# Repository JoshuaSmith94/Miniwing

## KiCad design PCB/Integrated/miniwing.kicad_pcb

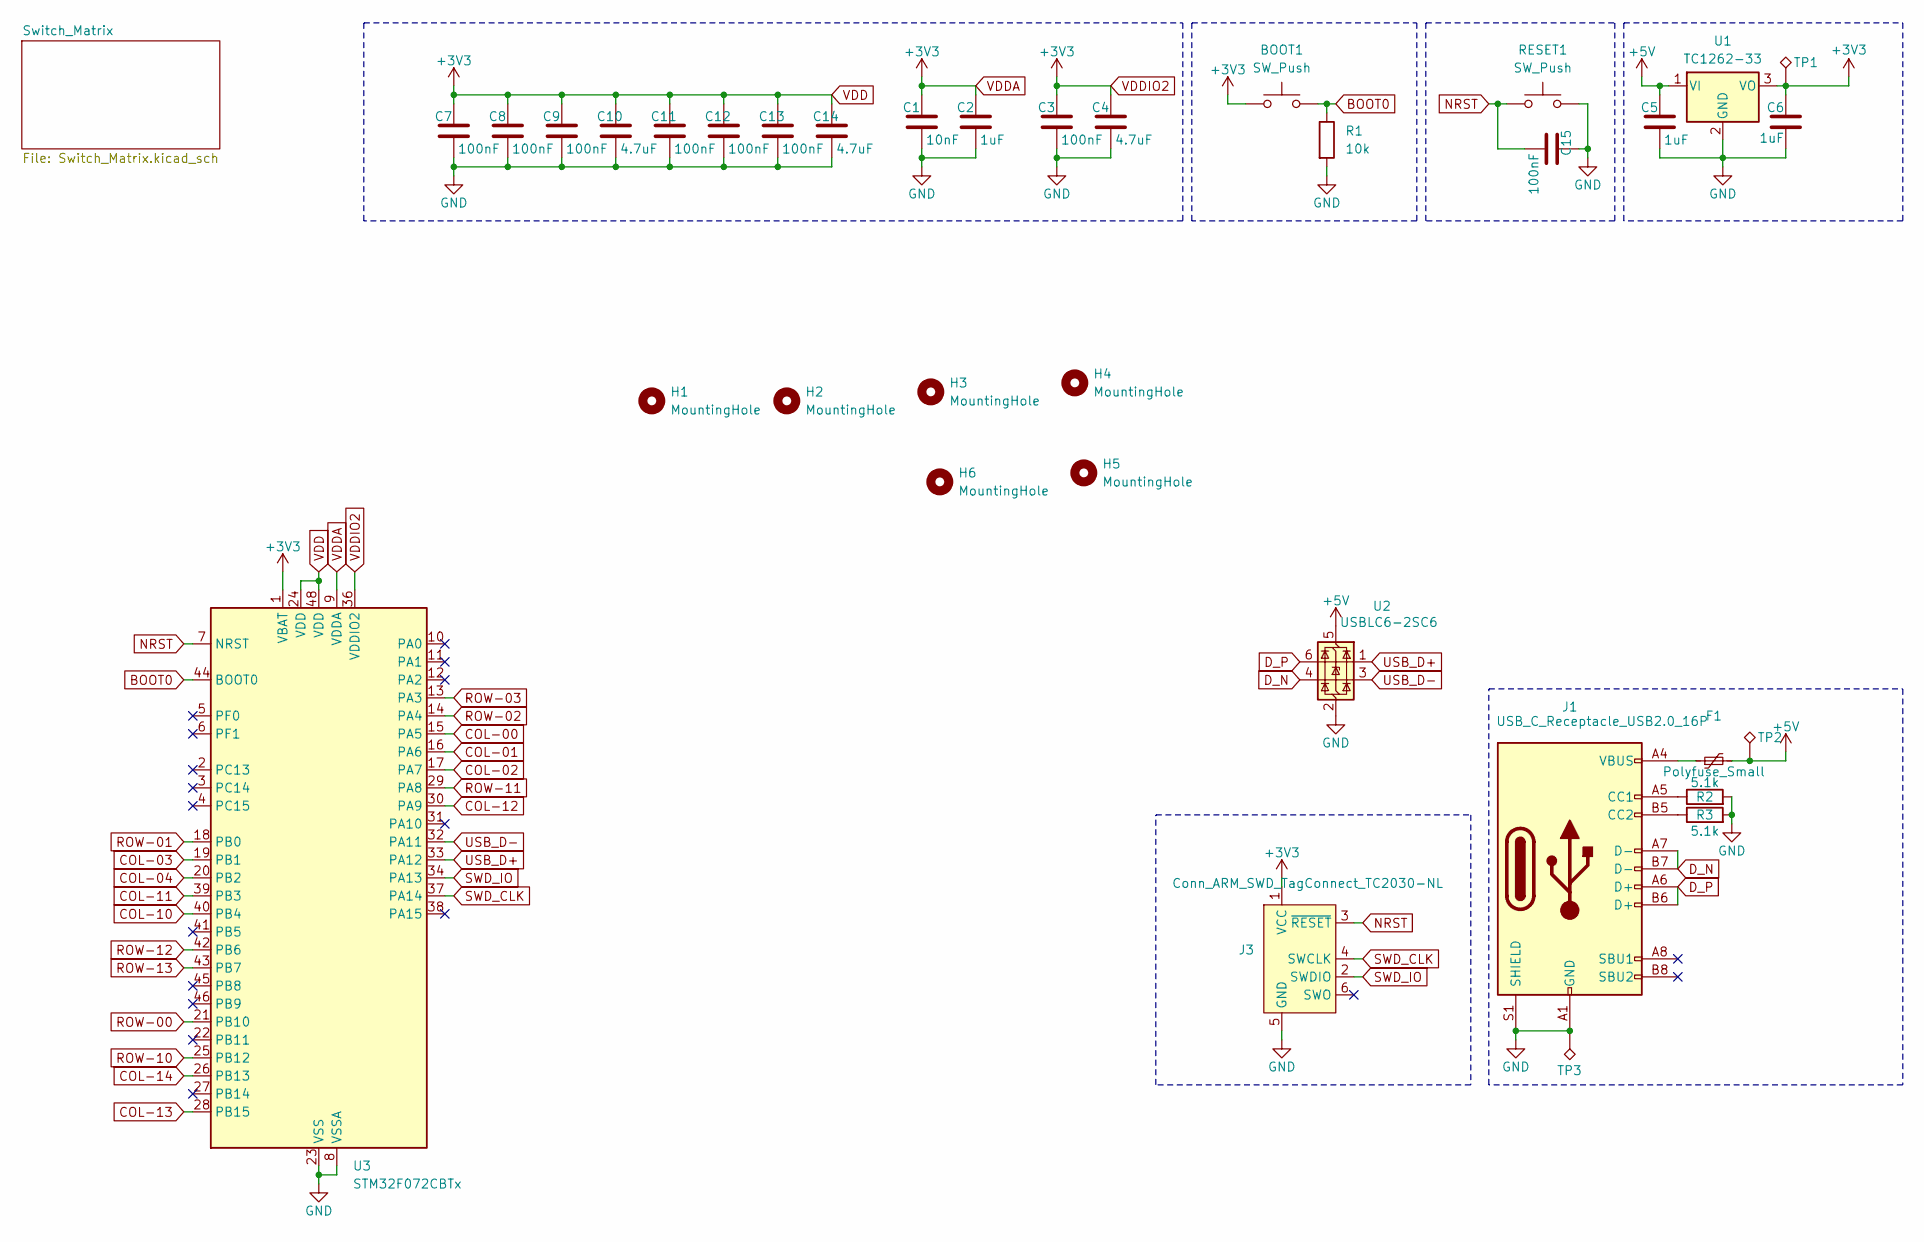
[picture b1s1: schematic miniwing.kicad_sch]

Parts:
BOOT1: SW_Push; SW_Push_1P1T_XKB_TS-1187A
C1: 10nF; C_0402_1005Metric
C2, C5, C6: 1uF; C_0402_1005Metric
C3, C7, C8, C9, C11, C12, C13, C15: 100nF; C_0402_1005Metric
C4, C10, C14: 4.7uF; C_0402_1005Metric
F1: Polyfuse_Small; Fuse_1812_4532Metric
H1, H2, H3, H4, H5, H6: MountingHole; MountingHole_3.2mm_M3
J1: USB_C_Receptacle_USB2.0_16P; USB_C_Receptacle_HRO_TYPE-C-31-M-12
J3: Conn_ARM_SWD_TagConnect_TC2030-NL; Tag-Connect_TC2030-IDC-NL_2x03_P1.27mm_Vertical
R1: 10k; R_0603_1608Metric
R2, R3: 5.1k; R_0603_1608Metric
RESET1: SW_Push; SW_Push_1P1T_XKB_TS-1187A
TP1, TP2, TP3: TestPoint_Alt; TestPoint_Pad_1.0x1.0mm
U1: TC1262-33; SOT-223-3_TabPin2
U2: USBLC6-2SC6; SOT-23-6
U3: STM32F072CBTx; LQFP-48_7x7mm_P0.5mm

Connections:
+5V: C5.1, F1.2, TP2.1, U1.1 (VI), U2.5 (VBUS)
BOOT0: BOOT1.2, R1.1, U3.44 (BOOT0)
COL-00: U3.15 (PA5); also elsewhere on the board
COL-01: U3.16 (PA6); also elsewhere on the board
COL-02: U3.17 (PA7); also elsewhere on the board
COL-03: U3.19 (PB1); also elsewhere on the board
COL-04: U3.20 (PB2); also elsewhere on the board
COL-10: U3.40 (PB4); also elsewhere on the board
COL-11: U3.39 (PB3); also elsewhere on the board
COL-12: U3.30 (PA9); also elsewhere on the board
COL-13: U3.28 (PB15); also elsewhere on the board
COL-14: U3.26 (PB13); also elsewhere on the board
D_N: J1.A7 (D-), J1.B7 (D-), U2.4 (I/O2)
D_P: J1.A6 (D+), J1.B6 (D+), U2.6 (I/O1)
GND: C1.2, C2.2, C3.2, C4.2, C5.2, C6.2, C7.2, C8.2, C9.2, C10.2, C11.2, C12.2, C13.2, C14.2, C15.1, J1.A1 (GND), J1.A12 (GND), J1.B1 (GND), J1.B12 (GND), J1.S1 (SHIELD), J3.5 (GND), R1.2, R2.2, R3.2, RESET1.2, TP3.1, U1.2 (GND), U2.2 (GND), U3.8 (VSSA), U3.23 (VSS), U3.35 (VSS), U3.47 (VSS)
NRST: C15.2, J3.3 (~RESET), RESET1.1, U3.7 (NRST)
unnamed: F1.1, J1.A4 (VBUS), J1.A9 (VBUS), J1.B4 (VBUS), J1.B9 (VBUS)
unnamed: J1.A5 (CC1), R2.1
unnamed: J1.B5 (CC2), R3.1
ROW-00: U3.21 (PB10); also elsewhere on the board
ROW-01: U3.18 (PB0); also elsewhere on the board
ROW-02: U3.14 (PA4); also elsewhere on the board
ROW-03: U3.13 (PA3); also elsewhere on the board
ROW-10: U3.25 (PB12); also elsewhere on the board
ROW-11: U3.29 (PA8); also elsewhere on the board
ROW-12: U3.42 (PB6); also elsewhere on the board
ROW-13: U3.43 (PB7); also elsewhere on the board
SWD_CLK: J3.4 (SWCLK), U3.37 (PA14)
SWD_IO: J3.2 (SWDIO), U3.34 (PA13)
USB_D+: U2.1 (I/O1), U3.33 (PA12)
USB_D-: U2.3 (I/O2), U3.32 (PA11)
VDD: BOOT1.1, C1.1, C2.1, C3.1, C4.1, C6.1, C7.1, C8.1, C9.1, C10.1, C11.1, C12.1, C13.1, C14.1, J3.1 (VCC), TP1.1, U1.3 (VO), U3.1 (VBAT), U3.9 (VDDA), U3.24 (VDD), U3.36 (VDDIO2), U3.48 (VDD)

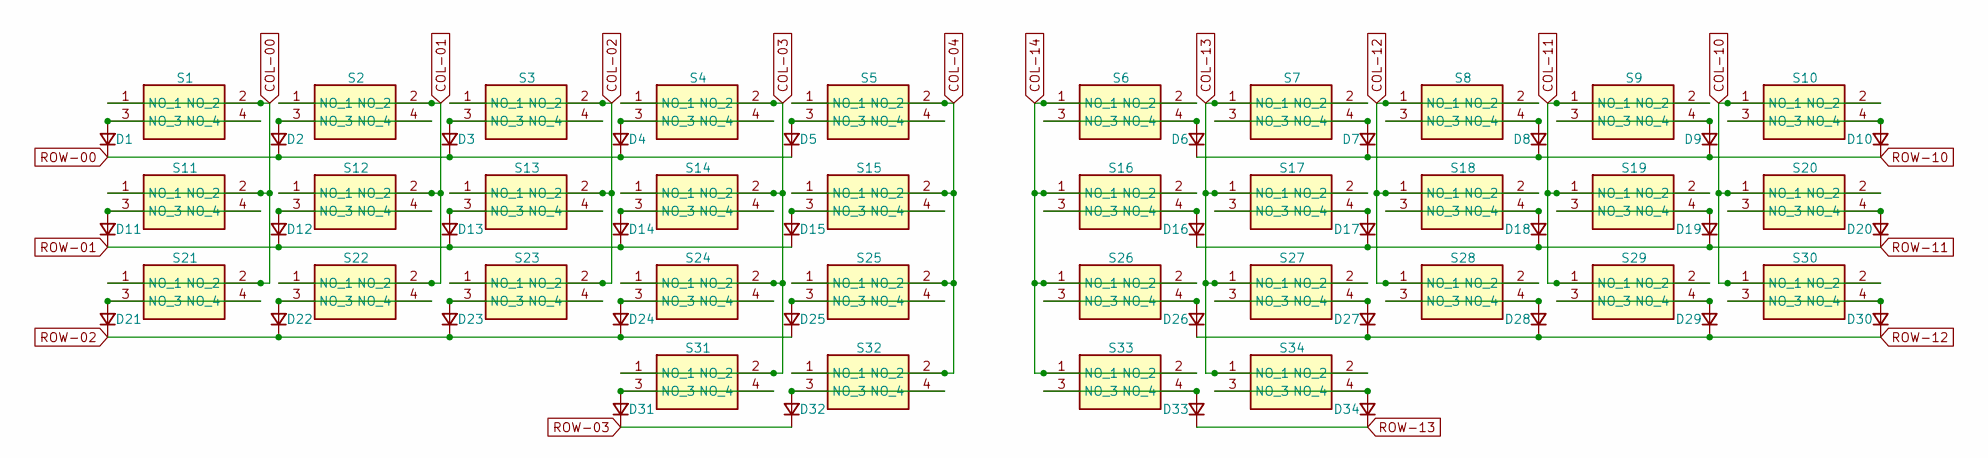
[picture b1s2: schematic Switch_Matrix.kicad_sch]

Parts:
D1, D2, D3, D4, D5, D6, D7, D8, D9, D10, D11, D12, D13, D14, D15, D16, D17, D18, D19, D20, D21, D22, D23, D24, D25, D26, D27, D28, D29, D30, D31, D32, D33, D34: 1N4148; D_SOD-323
S1, S2, S3, S4, S5, S6, S7, S8, S9, S10, S11, S12, S13, S14, S15, S16, S17, S18, S19, S20, S21, S22, S23, S24, S25, S26, S27, S28, S29, S30, S31, S32, S33, S34: SKHCBKA010; Mouser Part Number 688-SKHCBKA010

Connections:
COL-00: S1.1 (NO), S1.2 (NO), S11.1 (NO), S11.2 (NO), S21.1 (NO), S21.2 (NO); also elsewhere on the board
COL-01: S2.1 (NO), S2.2 (NO), S12.1 (NO), S12.2 (NO), S22.1 (NO), S22.2 (NO); also elsewhere on the board
COL-02: S3.1 (NO), S3.2 (NO), S13.1 (NO), S13.2 (NO), S23.1 (NO), S23.2 (NO); also elsewhere on the board
COL-03: S4.1 (NO), S4.2 (NO), S14.1 (NO), S14.2 (NO), S24.1 (NO), S24.2 (NO), S31.1 (NO), S31.2 (NO); also elsewhere on the board
COL-04: S5.1 (NO), S5.2 (NO), S15.1 (NO), S15.2 (NO), S25.1 (NO), S25.2 (NO), S32.1 (NO), S32.2 (NO); also elsewhere on the board
COL-10: S10.1 (NO), S10.2 (NO), S20.1 (NO), S20.2 (NO), S30.1 (NO), S30.2 (NO); also elsewhere on the board
COL-11: S9.1 (NO), S9.2 (NO), S19.1 (NO), S19.2 (NO), S29.1 (NO), S29.2 (NO); also elsewhere on the board
COL-12: S8.1 (NO), S8.2 (NO), S18.1 (NO), S18.2 (NO), S28.1 (NO), S28.2 (NO); also elsewhere on the board
COL-13: S7.1 (NO), S7.2 (NO), S17.1 (NO), S17.2 (NO), S27.1 (NO), S27.2 (NO), S34.1 (NO), S34.2 (NO); also elsewhere on the board
COL-14: S6.1 (NO), S6.2 (NO), S16.1 (NO), S16.2 (NO), S26.1 (NO), S26.2 (NO), S33.1 (NO), S33.2 (NO); also elsewhere on the board
unnamed: D1.2 (A), S1.3 (NO), S1.4 (NO)
unnamed: D2.2 (A), S2.3 (NO), S2.4 (NO)
unnamed: D3.2 (A), S3.3 (NO), S3.4 (NO)
unnamed: D4.2 (A), S4.3 (NO), S4.4 (NO)
unnamed: D5.2 (A), S5.3 (NO), S5.4 (NO)
unnamed: D6.2 (A), S6.3 (NO), S6.4 (NO)
unnamed: D7.2 (A), S7.3 (NO), S7.4 (NO)
unnamed: D8.2 (A), S8.3 (NO), S8.4 (NO)
unnamed: D9.2 (A), S9.3 (NO), S9.4 (NO)
unnamed: D10.2 (A), S10.3 (NO), S10.4 (NO)
unnamed: D11.2 (A), S11.3 (NO), S11.4 (NO)
unnamed: D12.2 (A), S12.3 (NO), S12.4 (NO)
unnamed: D13.2 (A), S13.3 (NO), S13.4 (NO)
unnamed: D14.2 (A), S14.3 (NO), S14.4 (NO)
unnamed: D15.2 (A), S15.3 (NO), S15.4 (NO)
unnamed: D16.2 (A), S16.3 (NO), S16.4 (NO)
unnamed: D17.2 (A), S17.3 (NO), S17.4 (NO)
unnamed: D18.2 (A), S18.3 (NO), S18.4 (NO)
unnamed: D19.2 (A), S19.3 (NO), S19.4 (NO)
unnamed: D20.2 (A), S20.3 (NO), S20.4 (NO)
unnamed: D21.2 (A), S21.3 (NO), S21.4 (NO)
unnamed: D22.2 (A), S22.3 (NO), S22.4 (NO)
unnamed: D23.2 (A), S23.3 (NO), S23.4 (NO)
unnamed: D24.2 (A), S24.3 (NO), S24.4 (NO)
unnamed: D25.2 (A), S25.3 (NO), S25.4 (NO)
unnamed: D26.2 (A), S26.3 (NO), S26.4 (NO)
unnamed: D27.2 (A), S27.3 (NO), S27.4 (NO)
unnamed: D28.2 (A), S28.3 (NO), S28.4 (NO)
unnamed: D29.2 (A), S29.3 (NO), S29.4 (NO)
unnamed: D30.2 (A), S30.3 (NO), S30.4 (NO)
unnamed: D31.2 (A), S31.3 (NO), S31.4 (NO)
unnamed: D32.2 (A), S32.3 (NO), S32.4 (NO)
unnamed: D33.2 (A), S33.3 (NO), S33.4 (NO)
unnamed: D34.2 (A), S34.3 (NO), S34.4 (NO)
ROW-00: D1.1 (K), D2.1 (K), D3.1 (K), D4.1 (K), D5.1 (K); also elsewhere on the board
ROW-01: D11.1 (K), D12.1 (K), D13.1 (K), D14.1 (K), D15.1 (K); also elsewhere on the board
ROW-02: D21.1 (K), D22.1 (K), D23.1 (K), D24.1 (K), D25.1 (K); also elsewhere on the board
ROW-03: D31.1 (K), D32.1 (K); also elsewhere on the board
ROW-10: D6.1 (K), D7.1 (K), D8.1 (K), D9.1 (K), D10.1 (K); also elsewhere on the board
ROW-11: D16.1 (K), D17.1 (K), D18.1 (K), D19.1 (K), D20.1 (K); also elsewhere on the board
ROW-12: D26.1 (K), D27.1 (K), D28.1 (K), D29.1 (K), D30.1 (K); also elsewhere on the board
ROW-13: D33.1 (K), D34.1 (K); also elsewhere on the board

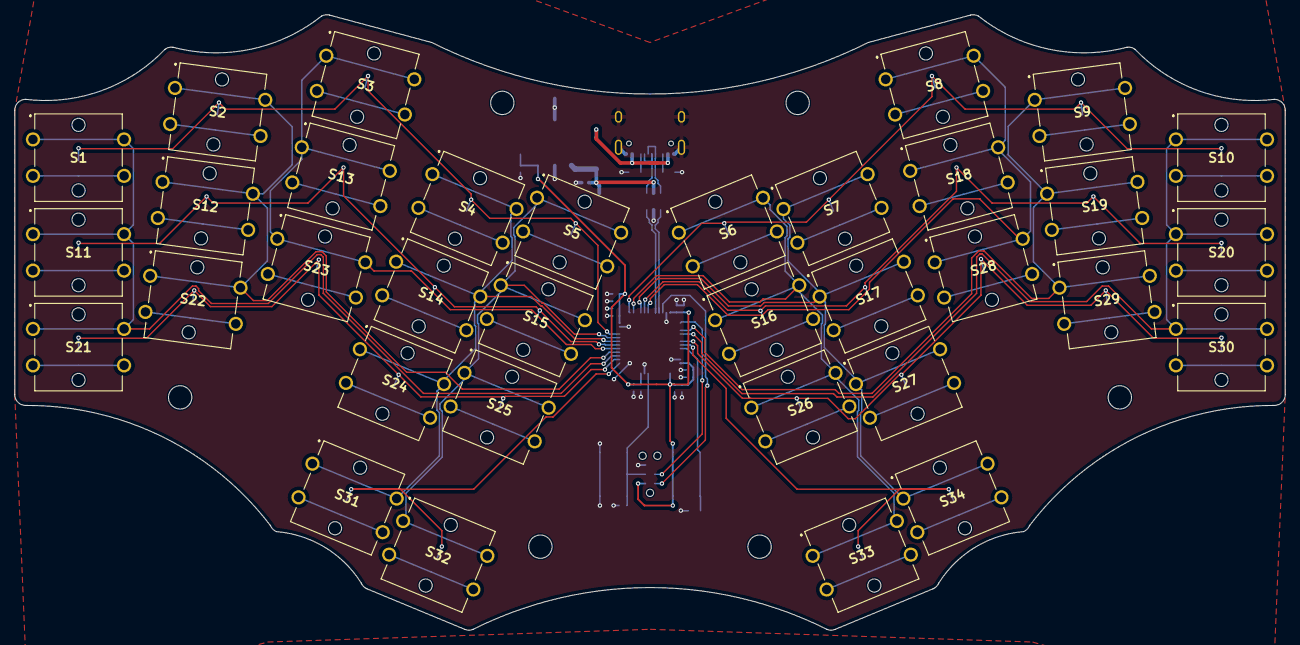
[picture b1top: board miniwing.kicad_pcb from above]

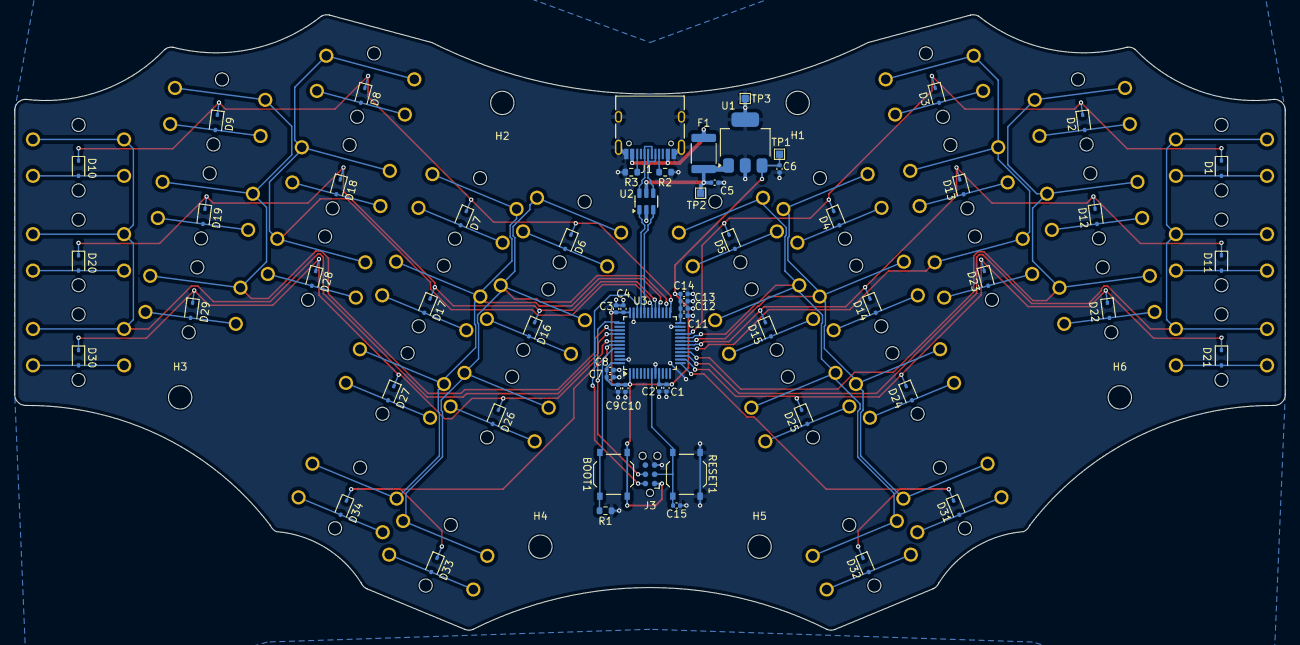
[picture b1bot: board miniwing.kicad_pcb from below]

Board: 2 copper layers, 174.3 x 84.4 mm, 103 parts (69 on the bottom side), 66 nets.

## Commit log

2025-01-25 Add PCB and QMK files.
2025-01-25 Split PCB into integrated and modular.
2025-02-01 Hopefully complete first version of integrated pcb.
2025-02-15 Added integrated qmk config.
